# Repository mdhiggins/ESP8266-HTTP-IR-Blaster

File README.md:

# IR Controller

ESP8266 Compatible IR Blaster that accepts HTTP commands for use with services like Amazon's Alexa

The purpose of this project was to create a Wi-Fi enabled IR blaster that could be controlled with Amazon Alexa
This was designed with the NodeMCU board but should be compatible with multiple ESP8266 variants

Includes a functional web portal for code capture, output monitoring, and device state tracking

Device gives real time LED feedback, can handle complex code sequences for multi-device home theater control, and full integration with Amazon Alexa via the smart home entertainment devices API and the `IR Controller` Alexa skill

Hardware
--------------

The hardware is based on the NodeMCU ESP8266 board and uses an infrared LED combined with the 2N2222 transistor for increased current and range. Values of the resistors seen in the schematic are variable and will depend on the specifications of your LED. If you're using the LED recommended below then a 1000 ohm resister to the 2N2222 transistor and a 10 ohm resistor to the LED itself are appropriate values, otherwise please use an LED resistance calculator. In total the parts come in around $10 so building a controller for each IR enabled device in your home is very feasible, and most components are cheaper in bulk

Shopping List:
- [ESP8266 NodeMCU Board](https://www.amazon.com/gp/product/B01IK9GEQG/)
- [IR Receiver](https://www.amazon.com/gp/product/B00EFOQEUM/)
- [Super bright IR Led](https://www.amazon.com/gp/product/B00ULB0U44/)
- [2N2222 Transistor](https://www.amazon.com/gp/product/B00R1M3DA4/)
- [Resistors](https://www.amazon.com/gp/product/B00YX75O5M/)

*These are just quick Amazon references. Parts can be purchased cheaper with longer shipping times from places like AliExpress*

Drivers
--------------
Install the NodeMCU drivers for your respective operating system if they are not autodetected

https://www.silabs.com/products/development-tools/software/usb-to-uart-bridge-vcp-drivers

Alexa Skill
--------------
The companion skill for the Amazon Alexa service is available [here](https://www.amazon.com/Michael-Higgins-IR-Controller/dp/B0762YYDS9) for US/CA/UK/IN/DE Alexa customers

Setup
--------------

If you use [PlatformIO](https://platformio.org/), you can clone the repository and run `platformio run -t upload` to
compile the library and upload it to a connected ESP8266-compatible board.

Otherwise, here are the building steps:

1. Install [Arduino IDE](https://www.arduino.cc/en/main/software)
2. Install [ESP8266 Arduino Core](https://github.com/esp8266/Arduino)
3. Install the following libraries from the Arduino IDE [Library Manager](https://www.arduino.cc/en/Guide/Libraries): `ESP8266WebServer` `ESP8266WiFi` `ArduinoJson` `Time` `IRremoteESP8266` as well as [`Cryptosuite`](https://github.com/jjssoftware/Cryptosuite) and the developer version of [`WiFiManager`] which is now on the IDE (version >= 2.0)
4. Load the `IRController.ino` blueprint from this repository
5. Upload blueprint to your ESP8266 (the .ino file). Monitor via serial at 115200 baud rate

After flashing, you can use the device like so:

1. Device will boot into WiFi access point mode initially with SSID `IR Controller Configuration`, IP address `192.168.4.1`. Connect to this and configure your access point settings using WiFi Manager. If your router supports mDNS/Bonjour you can now access your device on your local network via the hostname you specified (`http://hostname.local:port/`), otherwise via its local IP address (this IP address is displayed on the serial output)
2. Forward whichever port your ESP8266 web server is running on so that it can be accessed from outside your local network, this is critical since Alexa commands come from Amazon's servers, not locally
3. Download the IR Controller Alexa skill and start creating your devices. Each IR command will require a URL which can be saved. Choose whichever functionality you desire. Information on creating the URLs can be found below

Alexa Setup
---------------
1. Download the `IR Controller` skill from the Alexa skill store
2. Login with your Amazon account
3. Go to https://tehpsyc.pythonanywhere.com/
4. Login with the same Amazon account you used for the skill login
5. Create a new device by specifying the friendlyName, endpointId, and description
6. Add whichever functionality you want your device to have by scrolling through the options on the page
7. Save your new device
8. Run device discovery on your echo device by saying "Alexa, discover devices" or via https://alexa.amazon.com/
9. Verify that your new device was discovered online or in the Alexa app and enjoy!

Server Info
---------------

You may access basic device information at `http://xxx.xxx.xxx.xxx:port/` (webroot)

Capturing Codes
---------------
Your last scanned code can be accessed via web at `http://xxx.xxx.xxx.xxx:port/` or via serial monitoring over USB at 115200 baud. Most codes will be recognized and displayed in the format `A90:SONY:12`. Make a note of the code displayed in the serial output as you will need it for your maker channel URL. If your code is not recognized scroll down the JSON section of this read me.

NodeMCU PCU
---------------
@raptordemon has created a PCB that works great with this project. Use version 1.5
https://easyeda.com/raptordemon/ESP8266_IR_blaster-f8f224faba554bf3bb6ce0e32759fc23

Basic Output
--------------
For sending simple commands such as a single button press, or a repeating sequence of the same button press, use the logic below. This is unchanged from version 1.
Parameters
- `pass` - password required to execute IR command sending
- `code` - IR code such as `A90:SONY:12`
- `address` - (optional) Additional address data for NEC codes. Hex format
- `pulse` - (optional) Repeat a signal rapidly. Default `1`
- `pdelay` - (optional) Delay between pulses in milliseconds. Default `100`
- `repeat` - (optional) Number of times to send the signal. Default `1`. Useful for emulating multiple button presses for functions like large volume adjustments or sleep timer
- `rdelay` - (optional) Delay between repeats in milliseconds. Default `1000`
- `out` - (optional) Set which IRsend present to transmit over. Default `1`. Choose between `1-4`. Corresponding output pins set in the blueprint. Useful for a single ESP8266 that needs multiple LEDs pointed in different directions to trigger different devices

Example:
`http://xxx.xxx.xxx.xxx:port/msg?code=A90:SONY:12&pass=yourpass`

JSON Scripting
--------------
For more complicated sequences of buttons, such a multiple button presses or sending RAW IR commands or Pronto commands, you may do an HTTP POST with a JSON object that contains an array of commands which the receiver will parse and transmit. Payload must be a JSON array of JSON objects. Password should still be specified as the URL parameter `pass`.

Please note that Pronto codes are often given in a hexadecimal format and need to be prefixed with `0x` to indicate as such or they will be incorrectly transmitted.

Parameters
- `data` - IR code data, may be simple HEX code such as `"A90"` or an array of int values when transmitting a RAW sequence
- `type` - Type of signal transmitted. Example `"SONY"`, `"RAW"`, `"Delay"` or `"Roomba"` (and many others)
- `length` - (conditional) Bit length, example `12`. *Parameter does not need to be specified for RAW or Roomba signals*
- `pulse` - (optional) Repeat a signal rapidly. Default `1`
- `pdelay` - (optional) Delay between pulses in milliseconds. Default `100`
- `repeat` - (optional) Number of times to send the signal. Default `1`. *Useful for emulating multiple button presses for functions like large volume adjustments or sleep timer*
- `rdelay` - (optional) Delay between repeats in milliseconds. Default `1000`
- `khz` - (conditional) Transmission frequency in kilohertz. Default `38`. *Only required when transmitting RAW signal*
- `address` - (optional) Additional address data used for NEC codes. Hex format
- `out` - (optional) Set which IRsend present to transmit over. Default `1`. Choose between `1-4`. Corresponding output pins set in the blueprint. Useful for a single ESP8266 that needs multiple LEDs pointed in different directions to trigger different devices.

3 Button Sequence Example JSON
```
[
    {
        "type":"nec",
        "data":"FF827D",
        "length":32,
        "repeat":3,
        "rdelay":800
    },
    {
        "type":"nec",
        "data":"FFA25D",
        "length":32,
        "repeat":3,
        "rdelay":800
    },
    {
        "type":"nec",
        "data":"FF12ED",
        "length":32,
        "rdelay": 1000
    }
]
```

Raw Example
```
[
    {
    "type":"raw",
    "data":[2450,600, 1300,600, 700,550, 1300,600, 700,550, 1300,550, 700,550, 700,600, 1300,600, 700,550, 700,550, 700,550, 700],
    "khz":38,
    "pulse":3
    }
]
```

Pronto Example
```
[
    {
    type:"pronto",
    data: [0x0000, 0x0069, 0x0007, 0x0000, 0x032a, 0x010e, 0x005a, 0x010e, 0x005a, 0x005a, 0x0168, 0x005a, 0x005a, 0x010e, 0x005a, 0x00b4, 0x005a, 0x01c2]
    }
]
```

JSON as URL
--------------
To send the signal using the IFTTT Maker channel or the IR Controller smart home skill, simply take your JSON payload and remove spaces and line breaks so that entire packet is on a single line, then added it to the URL using the `plain` argument.

Sample URL using the same 3 button JSON sequence as above
```
http://xxx.xxx.xxx.xxx:port/json?pass=yourpass&plain=[{"type":"nec","data":"FF827D","length":32,"repeat":3,"rdelay":800},{"type":"nec","data":"FFA25D","length":32,"repeat":3,"rdelay":800},{"type":"nec","data":"FF12ED","length":32,"rdelay":1000}]
```

Determine Device State
--------------

To lookup and determine the state of the device, make an HTTP rest call to the `/state` endpoint.

Sample URL
```
http://xxx.xxx.xxx.xxx:port/state?pass=yourpass&device=yourdevice
```

Example Response:
```
{"status":"OK","state":1}
```

Security
---------------
Due to limitations imposed by the hardware in the ESP8266, there is not enough free memory to communicate over HTTPS/SSL. To protect your devices, during the WiFiManager setup process you can specify your Amazon user_id which will act as a secret key that allows SHA256 HMAC authentication to take place. Without this time sensitive signature no codes will be sent from the device. The user_id is a unique identifier tied to your account and my developer account, not shared across any other Amazon services. This unique ID can be found at the bottom of the tehpsyc.pythonanywhere.com page. The format is `amzn1.account.xxx`, **NOT your account email**. Enabling this feature will prevent sending commands via other means but greatly increases the security of the device. By default the option `bypassLocalAuth` is set to `true` which will allow requests made to the device coming from your local network (based on your local IP address and subnet) to be processed without the HMAC authentication.

To send commands over SSL you can use an intermediate service such as Smartthings (see below), use a reverse proxy with HTTPS support (which should work with the native Alexa skill) such a nginx, or handle everything on the local network and not use the functionality with Alexa.

This article provides some details on using nginx
https://jjssoftware.github.io/secure-your-esp8266/

Multiple LED Setup
--------------
If you are setting up your ESP8266 IR Controller to handle multiple devices, for example in a home theater setup, and the IR receivers are in different directions, you may use the `out` parameter to transmit codes with different LEDs which can be arranged to face different directions. Simply wire additional LEDs to a different GPIO pin on the ESP8266 in a similar fashion to the default transmitting pin and set the corresponding pin to the `irsend1-4` objects created at the top of the blueprint. For example if you wired an additional LED to the GPIO0 pin and you wanted to send a signal via that LED instead of the primary, you would modify irsend2 in the blueprint to `IRsend irsend2(0)` corresponding to the GPIO pin. Then when sending your signal via the url simply add `&out=2` and the signal will be sent via irsend2 instead of the primary irsend1.

Default mapping
- irsend1: GPIO4
- irsend2: GPIO5
- irsend3: GPIO12
- irsend4: GPIO13
- irrecv: GPIO14
- config: GPIO10

Force WiFi Reconfiguration
---------------
Set GPIO10 to ground to force a WiFi configuration reset, this will boot the device into WiFi host mode with an SSID of 'IR Controller Configuration' and IP of `192.168.4.1`

Device State Memory
---------------
By adding the `device` and `state` parameters to your URL or JSON object, the device will remember the last sent state of the device. This is useful since Alexa has separate on and off commands, and without knowing the device state will end up turning the TV on if an off command is issued

Example Turn On URL (if TV was already turned on, this command will do nothing):
`http://xxx.xxx.xxx.xxx:port/msg?code=A90:SONY:12&pass=yourpass&device=tv&state=1`

Example Turn Off URL (if TV was already turned off, this command will do nothing):
`http://xxx.xxx.xxx.xxx:port/msg?code=A90:SONY:12&pass=yourpass&device=tv&state=0`

Minimal Output
---------------
For configuring URLs to work with IFTTT or the IR Controller skill, or other automation services where the HTML output of the device will never be seen by a human, add `&simple=1` to the URL to simplify the data sent and speed up the response time

Example:
`http://xxx.xxx.xxx.xxx:port/msg?code=A90:SONY:12&pass=yourpass&simple=1`

IFTTT
--------------
If you are unable to use the Alexa skill for whatever reason, or you are using a competing voice control product or some other implementation, then IFTTT can also be used to execute commands using the Maker channel HTTP commands. Simply generate your URLs and save them in the Maker channel

Smartthings
--------------
For a great write up and instructional on how to integrate this device with Smartthings please visit http://thingsthataresmart.wiki/index.php?title=How_to_Control_your_TV_through_Alexa_and_Smartthings

Thanks to @dham102

Roku
--------------
The Roku device supports sending commands via an API to simulate remote button presses over HTTP, but only allows connections via a local IP address. This blueprint supports sending these commands and acts as a bridge between IFTTT/Alexa to control the Roku with basic commands

Roku commands require 3 parameters that can be sent as a Simple URL or part of a JSON collection. Parameters include:
- `data` - [Roku code](https://sdkdocs.roku.com/display/sdkdoc/External+Control+Guide)
- `type` - Type of signal transmitted. Must be set to `roku`
- `ip` - Local IP address of your Roku device

Example Roku command to simulate pressing play button on a Roku with local IP `10.0.1.3`
```
http://xxx.xxx.xxx.xxx:port/msg?pass=yourpass&type=roku&data=keypress/play&ip=10.0.1.3
```

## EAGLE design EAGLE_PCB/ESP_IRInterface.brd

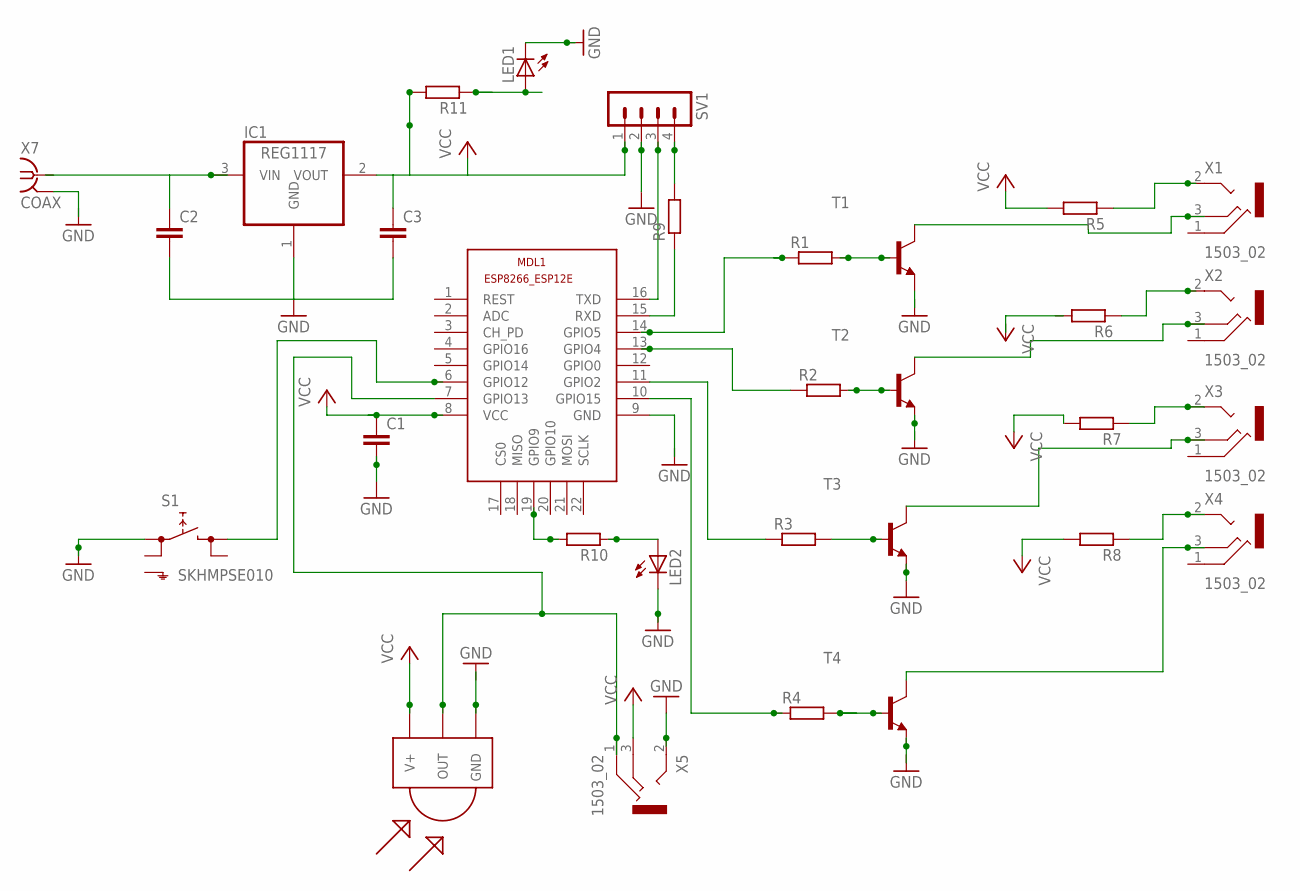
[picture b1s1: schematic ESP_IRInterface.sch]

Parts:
C1, C2, C3: CC1206; C1206
IC1: REG1117; SOT223
LED1, LED2: LED_E; LED_1206
MDL1: ESP8266-12EESP8266-ESP12E; ESP8266-ESP12E
R1, R2, R3, R4, R5, R6, R7, R8, R9, R10, R11: RR1206; R1206
S1: SKHMPSE010; SKHMPXE010
SV1: MA04-1
T1, T2, T3, T4: MMBT2222ALT1-NPN-SOT23-BEC; SOT23-BEC
TSOP1: TSOP1730; TSOP17XX
X1, X2, X3, X4, X5: 1503_02
X7: COAX; MMCX-J-P-X-ST-EM1-MKT

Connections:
GND: C1.2, LED1.C, LED2.C, S1.1 (1.1), SV1.2, T2.E, T3.E, X5.2, X7.2@2 (GND), X7.2@3 (GND), X7.2@4 (GND)
unnamed: C2.2, C3.2, IC1.1 (GND)
unnamed: MDL1.7 (GPIO13), TSOP1.OUT, X5.1
unnamed: MDL1.15 (RXD), R9.1
unnamed: MDL1.10 (GPIO15), R4.1
unnamed: MDL1.11 (GPIO2), R3.1
unnamed: MDL1.13 (GPIO4), R2.1
unnamed: MDL1.14 (GPIO5), R1.1
unnamed: R1.2, T1.B
unnamed: R2.2, T2.B
unnamed: R3.2, T3.B
unnamed: R4.2, T4.B
unnamed: R5.1, X1.2
unnamed: R6.1, X2.2
unnamed: R7.1, X3.2, X3.2@2 (2)
unnamed: R8.1, X4.2, X4.2@2 (2)
unnamed: T1.C, X1.3
unnamed: T2.C, X2.3
unnamed: T3.C, X3.3
unnamed: T4.C, X4.3
unnamed: C2.1, IC1.3 (VIN)
unnamed: R9.2, SV1.4
unnamed: MDL1.16 (TXD), SV1.3
unnamed: LED1.A, R11.1
unnamed: MDL1.6 (GPIO12), S1.3 (2.1)
unnamed: MDL1.19 (GPIO9), R10.2
unnamed: LED2.A, R10.1
VCC: C1.1, C3.1, IC1.2 (VOUT), MDL1.8 (VCC), R5.2, R7.2, R8.2, R11.2, SV1.1, TSOP1.V+, X5.3

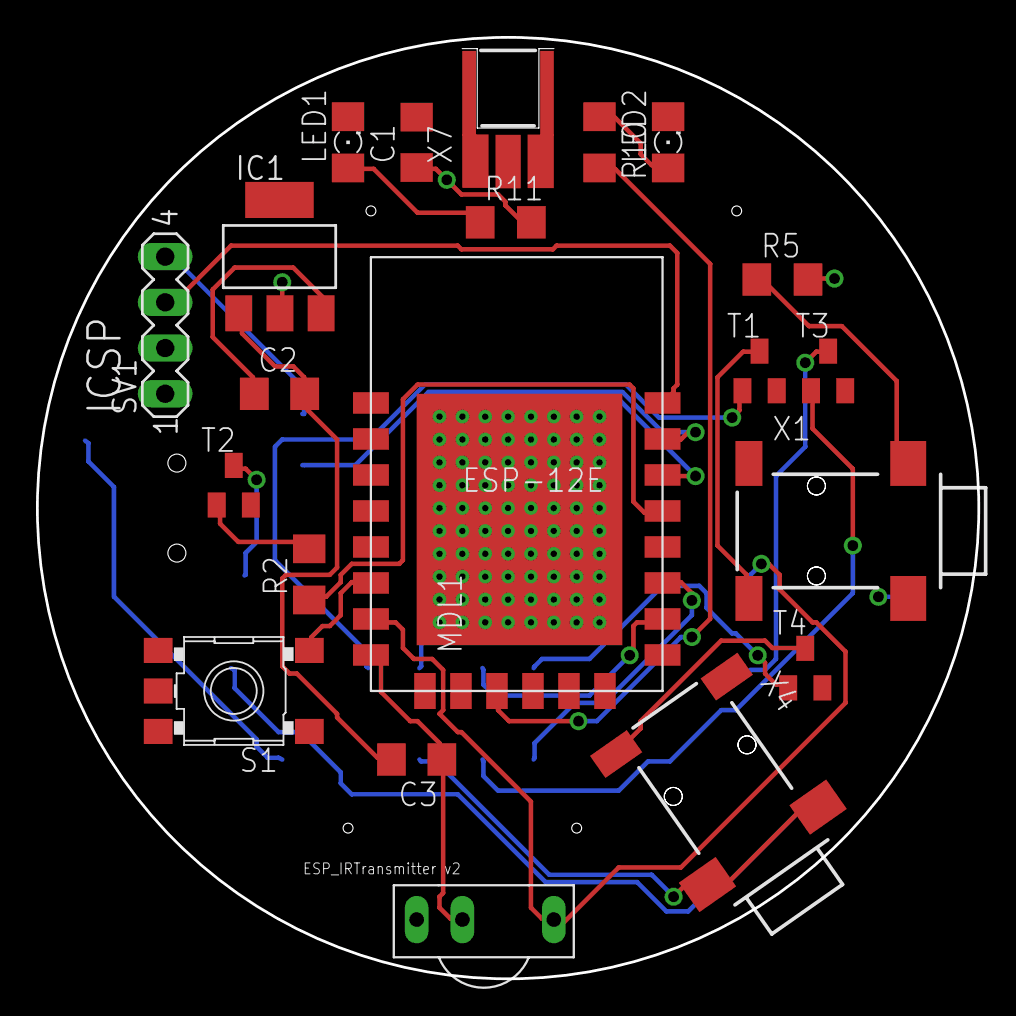
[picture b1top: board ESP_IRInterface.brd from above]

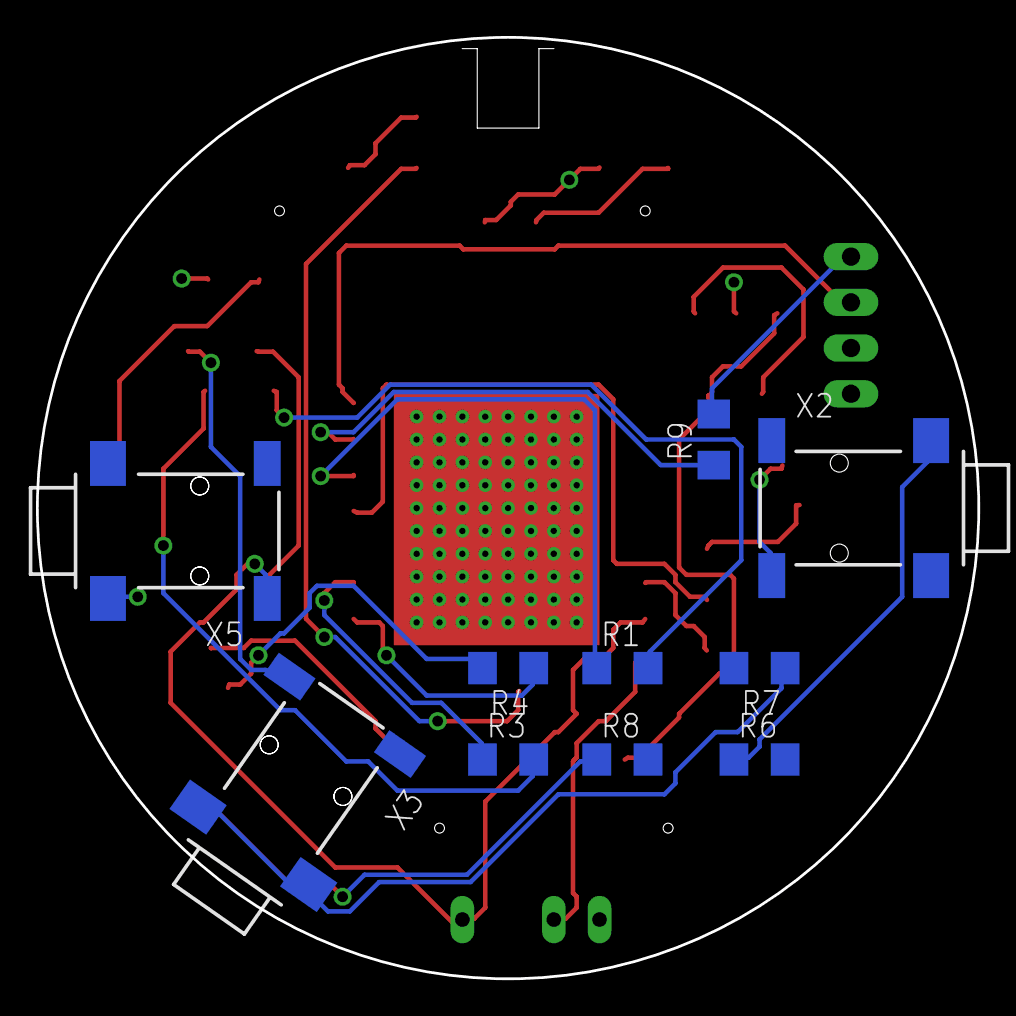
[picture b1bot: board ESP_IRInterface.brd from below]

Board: 2 copper layers, 52.3 x 52.3 mm, 31 parts (10 on the bottom side), 28 nets.

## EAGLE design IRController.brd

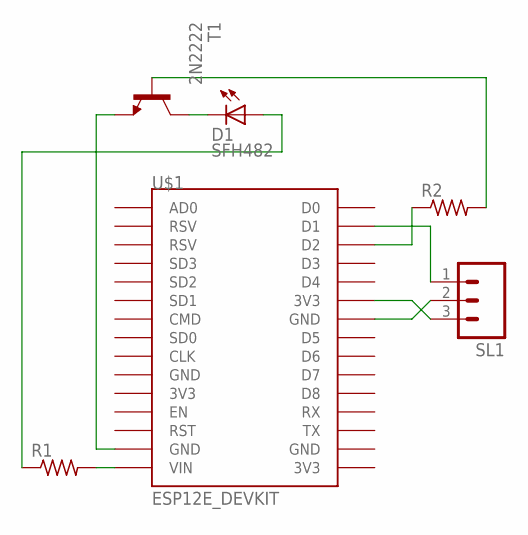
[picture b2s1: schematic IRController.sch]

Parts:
D1: SFH482
R1, R2: R-US_0204/2V; 0204V
SL1: MA03; 03P
T1: 2N2222; TO18
U$1: ESP12E_DEVKIT

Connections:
unnamed: SL1.1, U$1.D1
unnamed: SL1.3, U$1.3V3@1 (3V3)
unnamed: SL1.2, U$1.GND@2 (GND)
unnamed: R2.1, U$1.D2
unnamed: R1.2, U$1.VIN
unnamed: D1.A, R1.1
unnamed: R2.2, T1.2 (B)
unnamed: D1.K (C), T1.3 (C)
unnamed: T1.1 (E), U$1.GND@1 (GND)

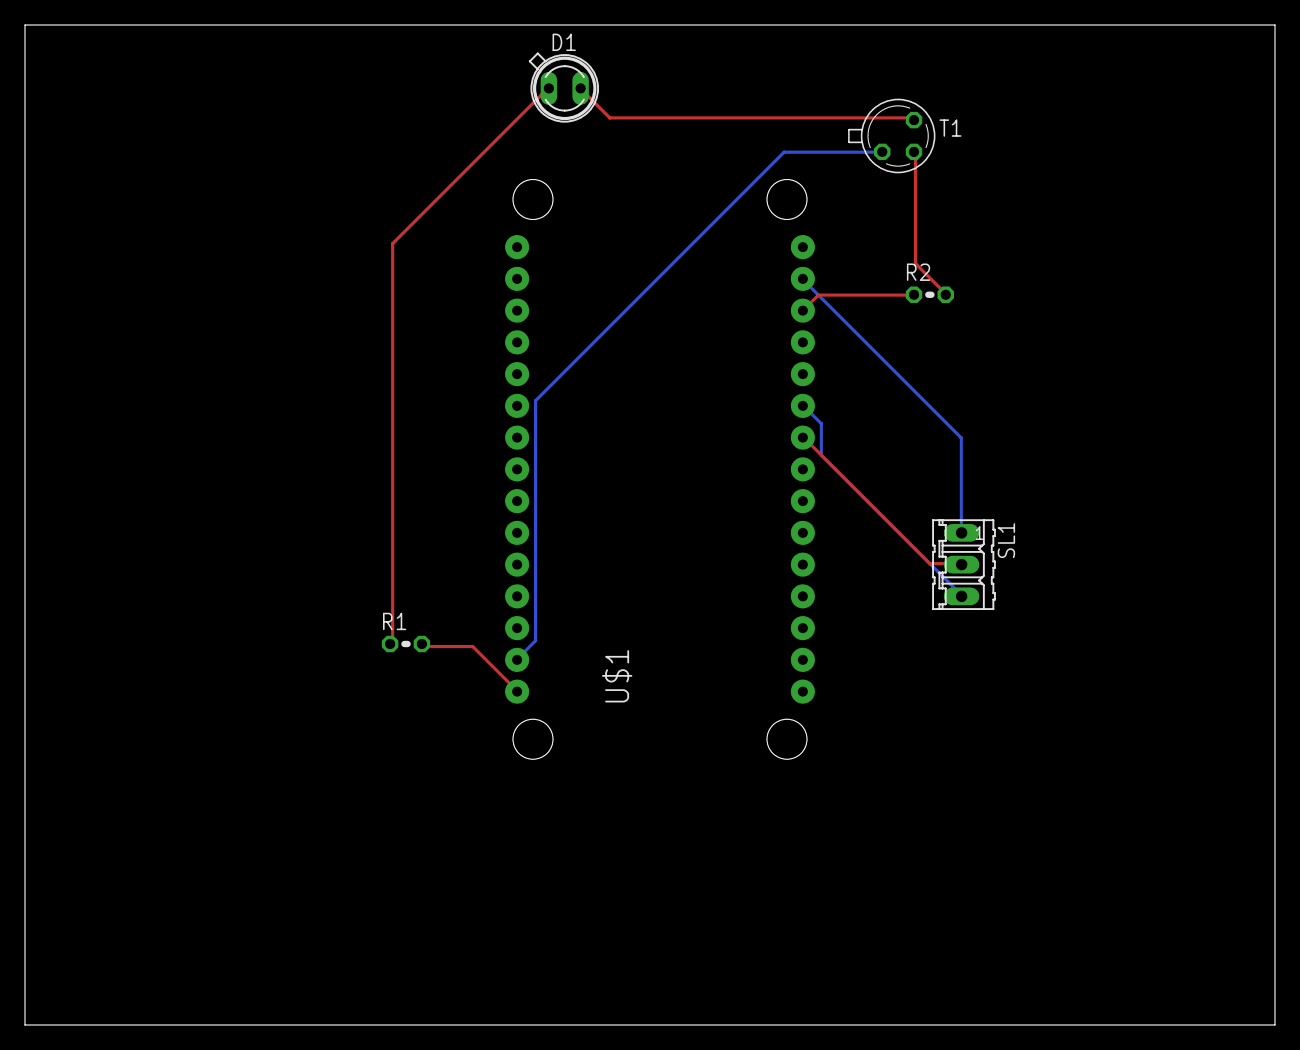
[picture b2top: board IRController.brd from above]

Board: 2 copper layers, 100.0 x 80.0 mm, 6 parts (0 on the bottom side), 9 nets.

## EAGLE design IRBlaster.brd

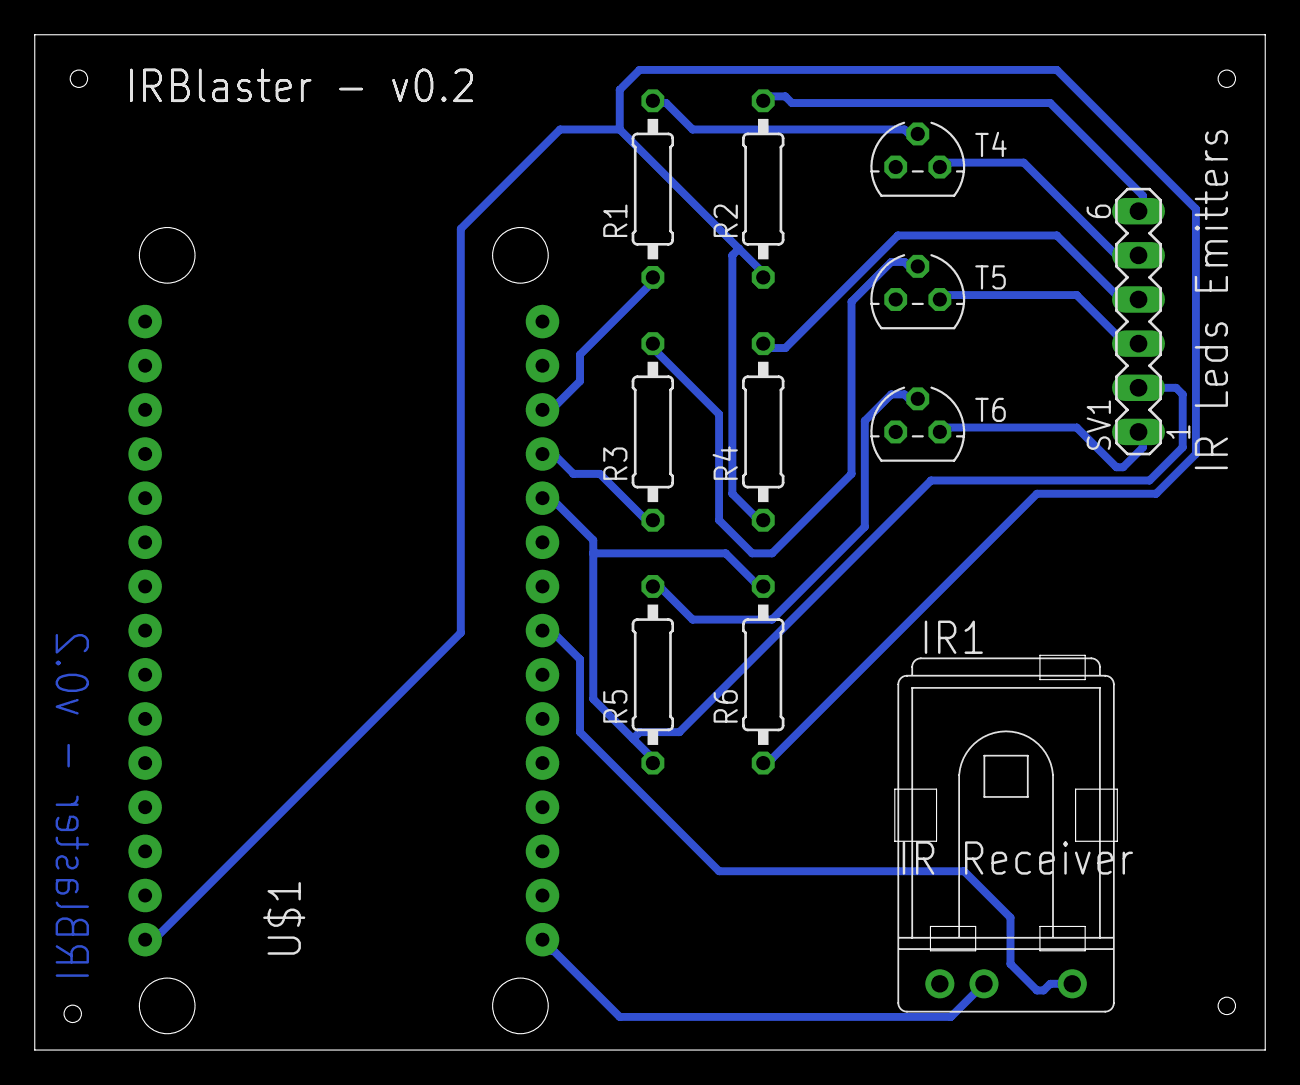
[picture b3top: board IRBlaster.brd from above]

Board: 2 copper layers, 70.8 x 58.4 mm, 12 parts (0 on the bottom side), 15 nets.

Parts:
IR1: TSOP1730TB1; TSOP17_TB1
R1, R3, R5: 1K; 0207/10
R2, R4, R6: 100; 0207/10
SV1: MA06-1
T4, T5, T6: 2N3904; TO92
U$1: ESP12E_DEVKIT

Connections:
GND: IR1.GND, T4.3, T5.3, T6.3, U$1.GND@3
unnamed: IR1.VO, U$1.D5
unnamed: R1.2, T4.2
unnamed: R3.2, T5.2
unnamed: R5.2, T6.2
unnamed: R4.2, SV1.4
unnamed: R2.2, SV1.6
unnamed: R1.1, U$1.D2
unnamed: SV1.5, T4.1
unnamed: R3.1, U$1.D3
unnamed: SV1.3, T5.1
unnamed: R5.1, R6.2, SV1.2, U$1.D4
unnamed: SV1.1, T6.1
VCC: R2.1, R4.1, R6.1, U$1.VIN
VCC/2: IR1.VS, U$1.3V3@2

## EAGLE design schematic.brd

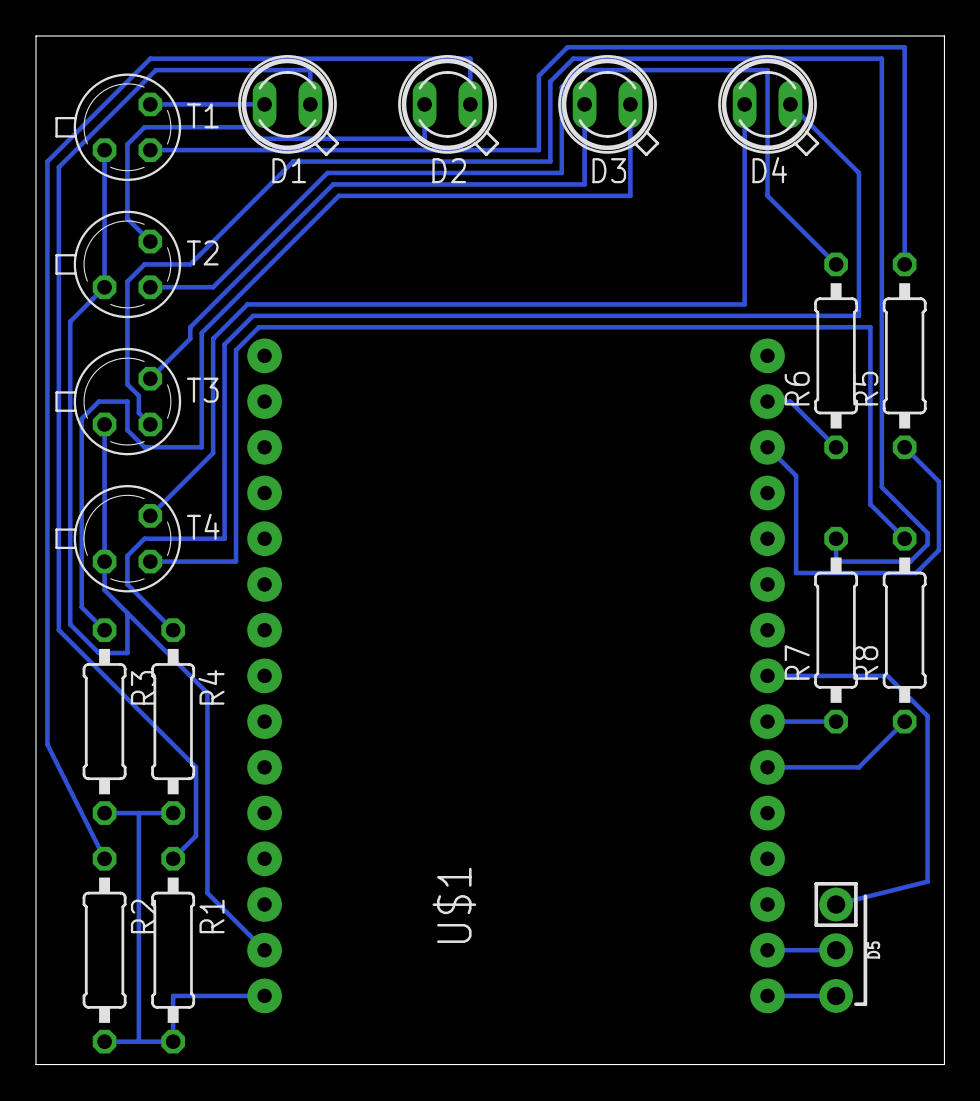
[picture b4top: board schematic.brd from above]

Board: 2 copper layers, 50.5 x 57.1 mm, 18 parts (0 on the bottom side), 21 nets.

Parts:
D1, D2, D3, D4: SFH482
D5: BRM-2A18RA; BRM-2508
R1, R2, R3, R4, R5, R6, R7, R8: 0207/10
T1, T2, T3, T4: 2N2222; TO18
U$1: ESP12_DEVKIT

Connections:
unnamed: R1.2, R2.2, R3.2, R4.2, U$1.5V
unnamed: D1.A, R1.1
unnamed: D2.A, R2.1
unnamed: D4.A, R4.1
unnamed: D1.K, T1.3
unnamed: D2.K, T2.3
unnamed: D3.K, T3.3
unnamed: D3.A, R3.1
unnamed: T1.1, T2.1, T3.1, T4.1, U$1.GND@1
unnamed: R5.2, T1.2
unnamed: R6.2, T2.2
unnamed: R7.2, T3.2
unnamed: R8.2, T4.2
unnamed: D5.3, U$1.3V3@2
unnamed: D5.2, U$1.GND@3
unnamed: D5.1, U$1.D5
unnamed: R5.1, U$1.D2
unnamed: R6.1, U$1.D1
unnamed: R7.1, U$1.D6
unnamed: R8.1, U$1.D7
unnamed: D4.K, T4.3

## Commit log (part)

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2016-12-09 BASIC code
2016-12-09 readme
2016-12-09 more readme cleanup
2016-12-10 update
    added support for pdelay and rdelay varialbes instead of hardcoding
    them to 10 and 1000ms
    added support for passing the IR directly through the URL instead of
    using the 1-6 boxes
2016-12-21 password support
2016-12-21 readme update
    includes the new password feature
2017-01-11 version 2 initial commit
    Removed basic language
    Included new arduino blueprint
    Readme update to follow
2017-01-11 readme update
    still needs lots of work
    need to include new hardware revisions that increase range
2017-01-11 sample update
2017-01-11 spelling error
2017-01-11 readme updates
2017-01-13 readme refinements
2017-01-14 support for using multiple IR leds
    readme update to follow
2017-01-14 multiple LED readme update
    cleaned parameter descriptions
    added out parameter documentation
    added small section explaining usage scenario
2017-01-19 rc5/rc6 fix
    did the other one too quickly
2017-01-19 roku support readme update
2017-01-21 http variable error fix
2017-01-24 readme url fix
2017-03-14 Software enhancements
    - let user configure wifi on first boot. no more
    need to hardcode the passwords
    - user can set the name of the blaster. Will be
    accessible on the local network through
    <name given by user>.local
    - bonjour service added
2017-03-17 Less power consumption
    Adding delay in the loop seems to help
    decreasing the power consumption.
    It does not impact the reaction time,
    around 6s for each command.
    Of course, rush of commands might be
    impacted
2017-05-12 readme update
    add WiFiManager to required packages
2017-05-12 readme update
    including default IRsend mapping
2017-05-13 fixes
    whitespace clean up
2017-05-13 clean up
2017-06-12 Added reference to custom PCB-set
    I designed a PCB and uploaded it to aisler to make ordering it simple.
2017-06-18 IRremoteESP8266 2.0 compatibility update
    Included changes required to make compatible with version 2.0 of the IR
    library
    Adjusted default GPIO send ports since 13 is the reset port now and 0
    prevents the device from booting if connected (flash)
2017-06-19 read code update
    Updated the methods for reading and outputting code to serial to be
    compliant with version 2.0
2017-06-19 readme update
    Includes new web features
2017-06-20 show last 3 codes
    instead of 1
2017-06-29 no negative values
2017-06-30 cosmetic patch
    increase stored codes to 5
    store sent codes as well
    new page to display the codes
    refer to new page for code sent/error pages
    new code summary page with example URLs and data
    Blink the light when a code is received
2017-06-30 side by side
2017-06-30 cache external IP
    reduces calls for external IP retrieval to speed up webpage delivery,
    defaults to rechecking every 72 hours
    Also increased the auto refresh frequency to every 5 minutes and
    removed the audio refresh from the code view page
2017-06-30 unneeded meta stuff
2017-06-30 ss update
2017-06-30 readme fixes
2017-06-30 html validation
    improved compliance with bootstraps protocol
    html validated and passing without errors
    UI inconsistencies fixed
2017-07-01 final updates
    consolidated the code
    improved compliance further
    subtle tweaks
2017-07-01 V3
    Huzzah
2017-07-01 allow disabling of externalIP query and NTP
    Reduces latency on systems with slow internet connection
    Added NTP re-sync every 72 hours
    Query external IP on boot
    Serial output for external IP query time
    Added a ‘!’ to header message
2017-07-02 HTML cleanup
    Fixed spacing for HTML so tabs are appropriate when viewing source
    Also added a “no codes sent/received” when no values are present for
    the table
2017-07-03 optimizations
    removed unneeded call to DNSServer.h
    added css override for nav-pills for mobile
2017-07-03 roku len 1
    style
2017-07-04 readme image resize
2017-07-04 make it bigger
2017-07-04 ws fix
2017-07-04 Revert "ws fix"
    This reverts commit 23c0f4d1f0255c6dd118ce60dc069820b999d5c8.
2017-07-08 adjust default pins
    Better for nodemcu compliance
    Additionally putting the receiver on GPIO14 lets the receiver be placed
    without additional wires
    Moved the LED flash when a command is received to the beginning
2017-07-09 remove old reference to sony pulse requirement
2017-07-12 false to 0
2017-07-23 raw fixes
    Fixed error when negative numbers were in the raw data using unsigned
    int would cause prolonged hang as they would be converted to very large
    positive numbers
    Added raw transmits to the list of codes being sent
    Added conditionals to clear data for codes that are missing certain
    elements
2017-08-09 update readme
    reflect new default IO pins
2017-09-28 improvements
    Efficiency improvements with simple response time; useful for in
    development accompanying Alexa skill
    Change reset pin to GPIO10 since 15 was variable and sometimes
    defaulted to LOW causing endless setting resets
    Added serial output to indicate reset pin state for debugging purposes
2017-10-01 added more codecs
    denon / lg / sanyo / rcmm
2017-10-01 name update
2017-10-03 sharp encoding support
2017-10-03 don't use sendSharp
    Its deprecated, misread the updates
    sendSharpRaw is the appropriate option
2017-10-05 global state for JSON
2017-10-05 Feedback
2017-10-10 Add EAGLE files for NodeMCU 0.9
    Single layer PCB layout for NodeMCU V0.9. This can be milled on a CNC.
2017-10-10 Add photos
2017-11-10 Default hostname to ESP Hostname
2017-11-11 Tuning
2017-11-13 Usability Improvements
2017-11-14 security readme update
2017-11-15 static IP
    Change from DHCP to static. Makes way more sense for this device since
    ports need to be forwarded
2017-11-18 better address handling
    Uses strtoul to handle HEX or DEC
2017-11-19 bugfix last pulse/repeat
2017-11-20 passcode adjustment
    do not fail passcode auth if one is in the url but no passcode is
    required
2017-11-22 timeClient refresh
    more reliable security check
2017-11-22 store ip as char
    instead of string
2017-11-27 Create folder
2017-11-27 Create dummy
2017-12-01 going international
2017-12-07 fix hostname
2017-12-08 get out of the upsidedown
2017-12-12 global and specific output for json
2017-12-18 Remove duplicate comment
2017-12-18 Add Gree support
2017-12-18 hostname fix
2017-12-20 URL encode data in example URLs
2017-12-28 eliminate hextolongint
    Not needed using strtoul
2017-12-28 blank address consistency
2017-12-30 alt inclusion
2018-01-07 2.4.0 compatability
    Update webserver to a pointer and initialize after port is defined from
    configuration
2018-01-07 error reporting
2018-01-08 cleanup
2018-01-10 lwIP DNS fix
2018-01-10 authentication validation
2018-01-11 pins
2018-01-14 Fix sending SharpRaw
2018-01-14 Don't make MAC address a clickable link
2018-01-15 Use uint64ToString from IRremoteESP8266
2018-01-16 better epoch error reporting
2018-01-17 Revert "Merge pull request #133 from zobotek/master"
    This reverts commit aebe57a1bdfb573436c1a1e59058e4c6c1766043, reversing
    changes made to cc4f9995c1dbf44adae11c93666d7161eeeea1bd.
2018-01-17 Increase the capture buffer size
    Allow users to alter the IR receive/capture buffer size without changing things in the underlying library.
2018-01-18 space
2018-01-27 new time server default
    updated time validation check at startup as well
2018-01-29 ntp error reporting
2018-03-25 show browser epoch time
    For comparison
    Still occasionally (though rarely) getting failures due to NTP syncing
    problems
2018-04-04 SMD round pcb
2018-06-17 Included detail on storing codes locally
    Updated to including some detail on storing and sending remote control commands
2018-06-21 Added state example to sendind
2018-06-21 Updated JSON receive section to handle state
    Updated to handle state for stored commands.
2018-07-02 add repeat and rdelay functionality to roku commands
2018-08-28 change ntp client
    also declare prototypes
    Had issue where script suddently wouldn't compile with a new computer, delcaring prototypes seems to fix
    add images used by Alexa skill icons
2018-09-25 Update to facilitate change to IRremoteESP8266 2.5
    As per the IRremoteESP8266 v.2.5, the following changes have been made:
    "The library has changed from using constants declared as #define to const with the appropriate naming per the C++ style guide. This may potentially cause old programs to not compile. The most likely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
    In the unlikely case it does break your code, then you may have been referencing something you likely should not have. You should be able to quickly determine the ne
2018-10-10 Add documentation in the README
2018-10-10 Downgrade to LwIP 1.4
2018-10-11 switch to correct board/version
2018-10-23 new time library
    ntpClient was having too many problems and not reliable, gonna try Time
2018-12-18 Update platformio.ini
    REMOVE old required EasyNTPClient and NTPClient libraries and ADD new required Time library.
2019-05-30 Migrate ArduinoJson from version 5 to 6
2019-06-01 Use library names instead of IDs, fix versions (code is incompatible with ArduinoJson v6)
2019-06-01 fix compile warning (comparing signed to unsigned int)
2019-07-30 fix ArduinoJson version
2019-08-17 Spelling fixes
2019-11-06 development fork
    tested using latest versions of arduinojson, wifimanager (dev branch), esp8266 core, and irremote
    can now have dynamic or static IP configuration options and can manually set DNS address which fixes lots of issues
    works with lwIP 2.0
2019-11-06 fix device state
    fix null devices for arduinojson 6
2019-11-06 git ignore
    update git ignore
2019-11-10 Send CORS headers in simple mode
2019-11-11 bootstrap 3.4.1
2020-04-24 update platformio
2020-04-25 fix platformio
2020-04-25 deprecation fix
2020-06-07 Update AP Name
    Update access point name to match what is in the code.
2020-06-07 fix SSID name
2020-06-15 Add DHCP setting
    Added a DHCP setting based upon the comments in previous issues:
    * enableDHCP = true will enable DHCP and disable static addresses
    * enableDHCP = false (default) will keep the current behaviour
2020-11-24 support AC control using JSON interface
2020-12-26 use typeToString
    replace outdated method
2020-12-27 remove development warning
2021-02-15 Set WiFi.mode(WIFI_STA) before WiFiManager
    Fix for issue: https://github.com/mdhiggins/ESP8266-HTTP-IR-Blaster/issues/307
2021-02-28 SPIFFS > LittleFS
    Since SPIFFS is deprecated
2021-03-14 additional board environments for platform IO
    nodemcuv2
    d1_mini
    d1_mini_lite
    d1_mini_pro
2021-03-14 add d1r1
2021-03-18 local bypass
    allow passcode to be bypassed for local traffic as well as the HMAC security
2021-04-24 Adding /send and /state endpoints for JSON Response and state checking
2021-04-24 Fixes and default state of 0 for devices
2021-04-29 Removing /send endpoint and updating readme for /state usage
2021-05-14 address
2021-05-22 mirror dev2
2021-05-22 Update IRController.ino
    reorganize
2021-05-24 state check
    include new state check endpoint
    consolidate security check into a dedicated function which reduces redundant code
    clean up text/html types to text/plain where appropriate
2021-05-25 Update IRController.ino
    further consolidate auth
    clean up
2021-05-26 Update IRController.ino
    spacing
2021-05-30 Update IRController.ino
    Limit last_send to 2 for memory conservation
    Write device states to LittleFS so that in the event of a crash/reset this data persists
    Erase states when device is reset
    Add a resetstates endpoint
2021-06-29 require core 2 for now
2021-06-29 Revert "Update IRController.ino"
    This reverts commit 657ebb25ce32031f794e65e1af5fcb04024b07e4.
2021-08-23 Update IRController.ino
    restore global jsondocument caching of device states
    allow states to be a string instead of just int
    remove before setting a value for existing keys
    fix missing ':' when sending all states
2021-08-24 Update IRController.ino
    disable device state caching, seems to corrupt for no reason

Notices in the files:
parts and their libraries:
sparkfun-sensors: Licensing: Creative Commons ShareAlike 4.0 International - https://creativecommons.org/licenses/by-sa/4.0
